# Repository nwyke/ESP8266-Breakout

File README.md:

# Breakoutboard for ESP8266

This board breaks out the pins from the ESP12E module, as well as holding some passives, which wires up to get you auto-reset to bootloader mode! Fits nicely on a breadboard.

Please support us and open-source hardware by purchasing products from
[MiniElektro.dk](http://minielektro.dk)/[MiniElektro.se](http://minielektro.se).

Content
-------------------
* **/Hardware**
  * All Eagle design files (.brd, .sch)

License
-------------------
The hardware is released under [Creative Commons ShareAlike 4.0 International](https://creativecommons.org/licenses/by-sa/4.0/).

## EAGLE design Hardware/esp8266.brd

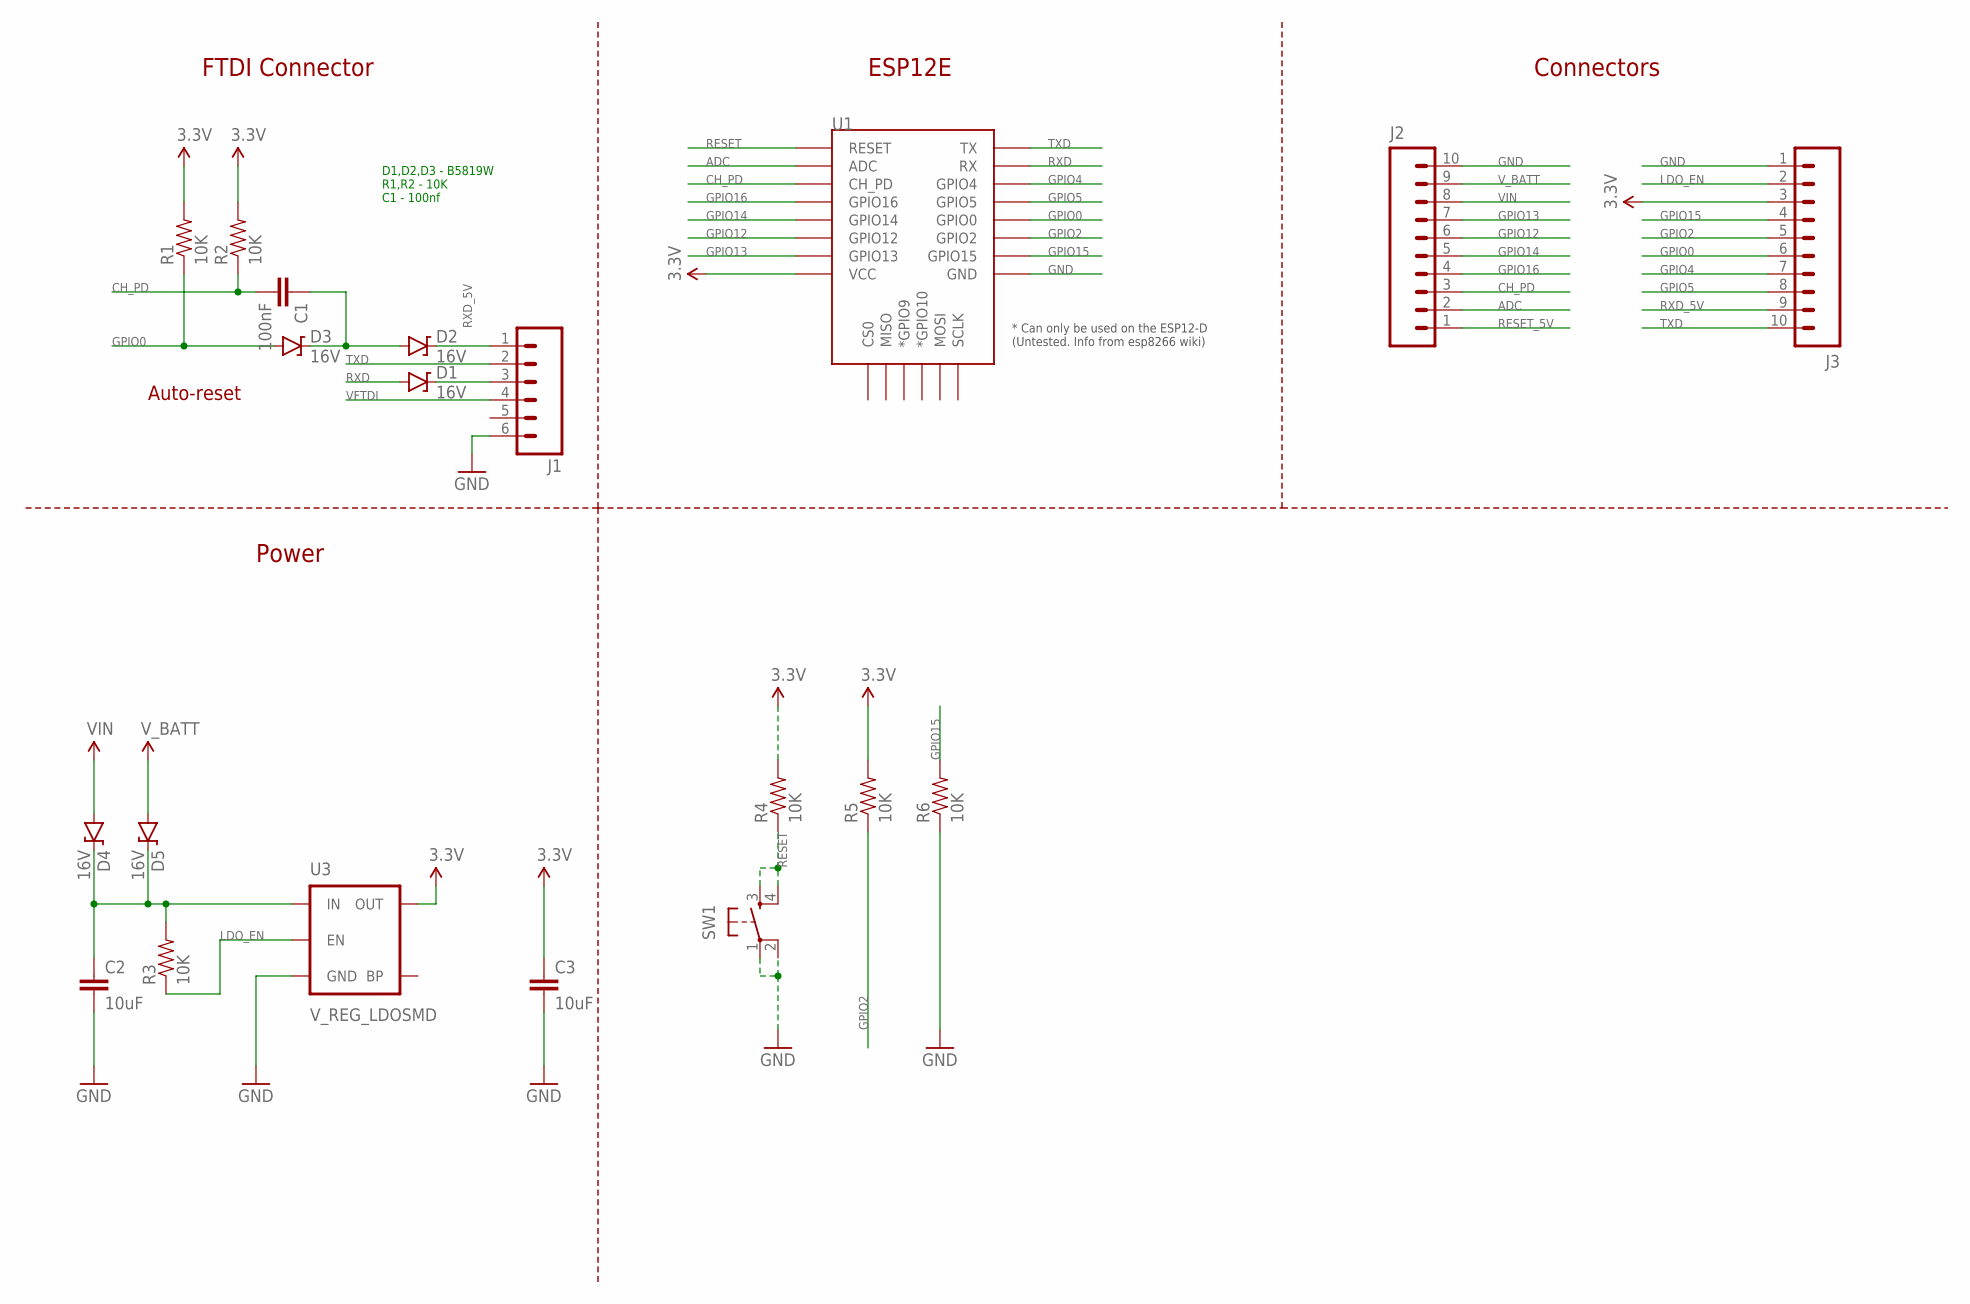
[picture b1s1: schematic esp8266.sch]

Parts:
C1: 100nF; 0402-CAP
C2, C3: 10uF; 0402-CAP
D1, D2, D3, D4, D5: 16V; SOD-123
J1: M06SILK_FEMALE_PTH; 1X06
J2, J3: M10SILK_FEMALE_PTH; 1X10
R1, R2, R3, R4, R5, R6: 10K; 0402-RES
SW1: SWITCH_SPST_4_PINRECT; TACTILE_SWITCH_SMD_4.6X2.8MM
U1: ESP12ESMD; ESP12E-SMD
U3: V_REG_LDOSMD; SOT23-5

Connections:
3.3V: C3.1, J3.3, R1.2, R2.2, R4.2, R5.2, U1.VCC, U3.5 (OUT)
ADC: J2.2, U1.ADC
CH_PD: C1.2, J2.3, R2.1, U1.CH_PD
GND: C2.2, C3.2, J1.6, J2.10, J3.1, R6.1, SW1.1, SW1.2, U1.GND, U3.2 (GND)
GPIO0: D3.A, J3.6, R1.1, U1.GPIO0
GPIO2: J3.5, R5.1, U1.GPIO2
GPIO4: J3.7, U1.GPIO4
GPIO5: J3.8, U1.GPIO5
GPIO12: J2.6, U1.GPIO12
GPIO13: J2.7, U1.GPIO13
GPIO14: J2.5, U1.GPIO14
GPIO15: J3.4, R6.2, U1.GPIO15
GPIO16: J2.4, U1.GPIO16
LDO_EN: J3.2, R3.1, U3.3 (EN)
unnamed: C2.1, D4.C, D5.C, R3.2, U3.1 (IN)
unnamed: D2.C, J1.1
unnamed: C1.1, D2.A, D3.C
RESET: R4.1, SW1.3, SW1.4, U1.RESET
RESET_5V: J2.1
RXD: D1.A, U1.RXD0 (RX)
RXD_5V: D1.C, J1.3, J3.9
TXD: J1.2, J3.10, U1.TXD0 (TX)
VFTDI: J1.4
VIN: D4.A, J2.8
V_BATT: D5.A, J2.9

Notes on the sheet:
D1,D2,D3 - B5819W R1,R2 - 10K C1 - 100nf
FTDI Connector
Auto-reset
ESP12E
Connectors
Power

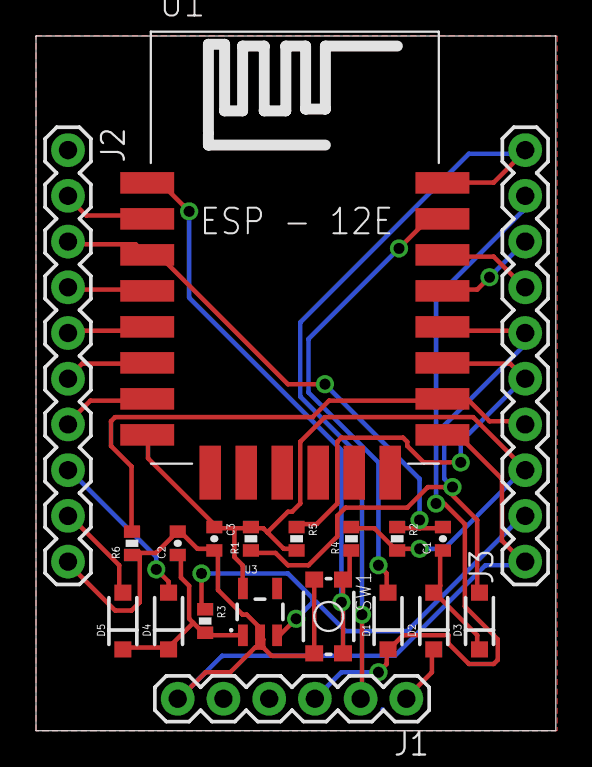
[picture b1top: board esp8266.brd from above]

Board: 2 copper layers, 28.9 x 38.6 mm, 20 parts (0 on the bottom side), 23 nets.

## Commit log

2016-05-20 Add description, content, license

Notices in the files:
parts and their libraries:
SparkFun-Passives: Licensing: Creative Commons ShareAlike 4.0 International - https://creativecommons.org/licenses/by-sa/4.0
